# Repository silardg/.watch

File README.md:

# Project watch with nRF 
nRF, accelerometer, gyroscope and a battery charger on the footprint of the nRF module

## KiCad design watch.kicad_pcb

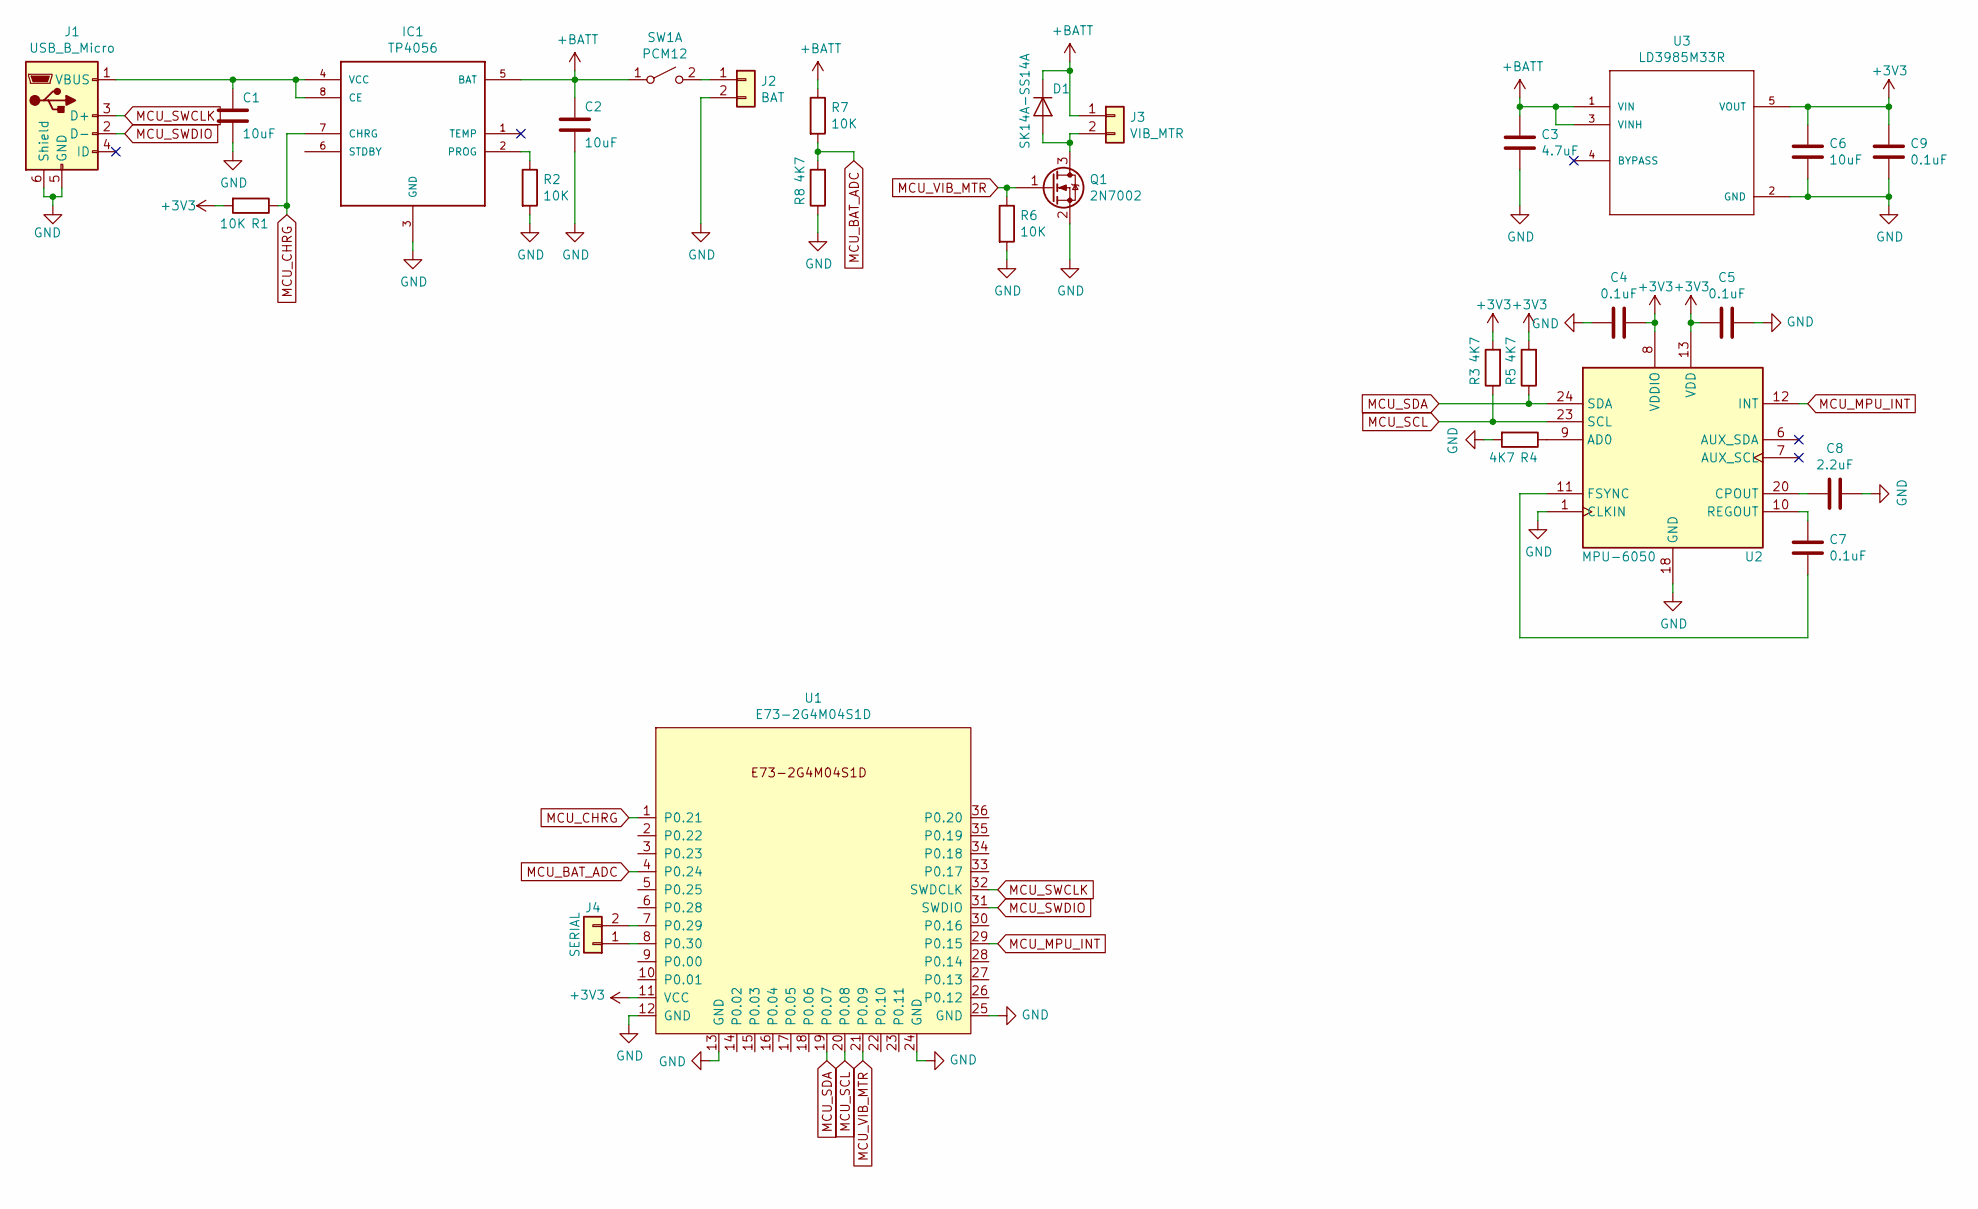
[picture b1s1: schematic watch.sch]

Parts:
C1, C2: 10uF; C_0805_2012Metric
C3: 4.7uF; C_0603_1608Metric
C4, C5, C7, C9: 0.1uF; C_0603_1608Metric
C6: 10uF; C_0603_1608Metric
C8: 2.2uF; C_0805_2012Metric
D1: SK14A-SS14A; D_SMA
IC1: TP4056; SOP-8
J1: USB_B_Micro; USB_Micro-B_Molex_47346-0001
J2: BAT; D_1210_3225Metric
J3: VIB_MTR; D_1210_3225Metric
J4: SERIAL; R_0603_1608Metric
Q1: 2N7002; SOT-23
R1, R2, R6, R7: 10K; R_0603_1608Metric
R3, R4, R5, R8: 4K7; R_0603_1608Metric
SW1: PCM12; SW_SPDT_PCM12
U1: E73-2G4M04S1D; E73-2G4M04S
U2: MPU-6050; InvenSense_QFN-24_4x4mm_P0.5mm
U3: LD3985M33R; SOT95P280X145-5N

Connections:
+3V3: C4.1, C5.2, C6.1, C9.1, R1.2, R3.2, R5.2, U1.11 (VCC), U2.8 (VDDIO), U2.13 (VDD), U3.5 (VOUT)
+BATT: C2.1, C3.1, D1.1 (K), IC1.5 (BAT), J3.1, R7.1, SW1.1 (A), U3.1 (VIN), U3.3 (VINH)
GND: C1.2, C2.2, C3.2, C4.2, C5.1, C6.2, C8.1, C9.2, IC1.3 (GND), J1.5 (GND), J1.6 (Shield), J2.2, Q1.2 (S), R2.2, R4.2, R6.2, R8.1, U1.12 (GND), U1.13 (GND), U1.24 (GND), U1.25 (GND), U2.1 (CLKIN), U2.18 (GND), U3.2 (GND)
MCU_BAT_ADC: R7.2, R8.2, U1.4 (P0.24)
MCU_CHRG: IC1.7 (CHRG), R1.1, U1.1 (P0.21)
MCU_MPU_INT: U1.29 (P0.15), U2.12 (INT)
MCU_SCL: R3.1, U1.20 (P0.08), U2.23 (SCL)
MCU_SDA: R5.1, U1.19 (P0.07), U2.24 (SDA)
MCU_SWCLK: J1.3 (D+), U1.32 (SWDCLK)
MCU_SWDIO: J1.2 (D-), U1.31 (SWDIO)
MCU_VIB_MTR: Q1.1 (G), R6.1, U1.21 (P0.09)
unnamed: C1.1, IC1.4 (VCC), IC1.8 (CE), J1.1 (VBUS)
unnamed: C7.1, U2.11 (FSYNC)
unnamed: C7.2, U2.10 (REGOUT)
unnamed: C8.2, U2.20 (CPOUT)
unnamed: D1.2 (A), J3.2, Q1.3 (D)
unnamed: IC1.2 (PROG), R2.1
unnamed: J2.1, SW1.2 (B)
unnamed: J4.1, U1.8 (P0.30)
unnamed: J4.2, U1.7 (P0.29)
unnamed: R4.1, U2.9 (AD0)

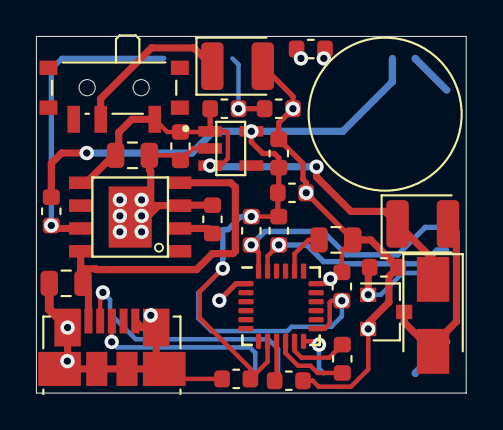
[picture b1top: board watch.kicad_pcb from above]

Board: 2 copper layers, 23.9 x 19.8 mm, 28 parts (1 on the bottom side), 21 nets.

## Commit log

2019-07-16 Add everything
2019-07-16 Added schematic
